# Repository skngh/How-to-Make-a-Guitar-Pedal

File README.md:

# How to Make a Digital Guitar Pedal

_by Sam Knight_

Welcome! This repository contains documentation and supporting materials for my YouTube course on how to build a digital guitar pedal using the Daisy Seed.

The goal of this course is not to clone a specific pedal, but to teach the full workflow and decision-making process behind designing, programming, and assembling your own digital guitar pedals.

## Table of Contents

- [Course Overview](#course-overview)
- [Prerequisites](#prerequisites)
- [Documentation & Resources](#documentation--resources)
  - [Bill of Materials](docs/bom.md)
  - [Resources & Links](docs/resources.md)
  - [Recommended Learning](docs/recommended-learning.md)
  - [Code](code/)
  - [Hardware](hardware/)
- [Episode Breakdown](#episode-breakdown)

## Course Overview

This course covers many topics, including:

- Setting up the **Daisy Seed** with a breadboard
- Programming a simple **hard clipping and soft clipping distortion**
- Using the **DaisySP library** to program the Daisy
- Making a **drill schematic on Tayda Electronics** for our enclosure
- Making a **full custom PCB in KiCad** with accurate part placements
- Designing a **graphic in Adobe Illustrator** to get **UV printed** onto our enclosure
- Ordering everything and **soldering** it all together

### Final Result

This does not mean it is the exact pedal you will end up with. The purpose of the course is to teach the fundamentals and workflow of digital pedal design, not to produce an identical clone. You are encouraged to experiment, modify, and build something that reflects your own ideas.

## Prerequisites!

This course is intended for beginners, but not all beginners start in the same place. While the course is designed to be approachable, there are areas where having absolutely no prior experience may create friction.

That said, even if you are completely new to this space, the course can still serve as a strong foundation. If your long-term goal is to design audio-related hardware or software, this course will help identify the gaps you may want to fill going forward.

You may find parts of the course challenging if you have no experience with the following:

1. **Basic programming.** I show you how to use the DaisySP library and teach very basic DSP, but if you haven't ever written a single line of code before, there will be confusing moments. I don't go over the very basics of programming in the course, but as long as you have a simple understanding of the building blocks of any programming language, then I think you'll be fine.
2. **Very basic understanding of electrical engineering.** Going forward, if something like a "resistor" means nothing to you, then you may hit a little bottleneck with designing pedals. Don't get me wrong, to design basic circuits like we do in this course, you don't have to design anything honestly, but if you want to keep improving that will be needed moving forward. And if you have zero understanding of wiring up components and things, then there may be moments of the course that get confusing.

## Episode Breakdown

### Episode 1 — Picking Parts

Setting up the Daisy Seed on a breadboard and selecting initial components so we can begin experimenting with knobs, switches, and basic interaction.

### Episode 2 — Basic DSP

An introduction to digital signal processing and the Daisy audio callback. We use these concepts to build simple hard-clipping and soft-clipping distortion effects.

### Episode 3 — DaisySP Library

A walkthrough of the DaisySP library and how to integrate its DSP modules into your projects. We implement a basic chorus effect as a practical example.

### Episode 4 — Enclosure Drill Schematic

Creating a drill schematic using Tayda Electronics so the enclosure arrives pre-drilled and ready for assembly.

### Episode 5 — Circuit Schematic

Designing a simple circuit schematic in KiCad to connect the Daisy Seed with external components.

### Episode 6 — Footprints

Learning how to find existing footprints and create custom footprints using component datasheets.

### Episode 7 — PCB Layout & Routing

Defining the PCB outline, placing components so the board fits correctly inside the enclosure and aligns with the drill schematic, and basic PCB routing and ground plane.

### Episode 8 — Design Review & Ordering

Verifying mechanical fit, checking for common errors, and ordering the PCB through PCBWay.

### Episode 9 — UV Printing & Final Parts Order

Designing enclosure artwork for UV printing and placing final parts orders.

### Episode 10 — Final Assembly

Soldering the pedal together, testing the hardware, and applying finishing touches to the firmware.

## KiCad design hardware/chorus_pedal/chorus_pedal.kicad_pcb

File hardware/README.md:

# Hardware

This folder contains all hardware-related files used throughout the course, including the PCB design, enclosure artwork, and drill schematic.

---

## PCB (KiCad)

The KiCad project files for the custom PCB designed during the course can be found in this folder.

- Open the KiCad project to view the schematic and PCB layout.
- These files correspond to [this code here.](../code/ChorusPedal/)

---

## Enclosure Graphic (Adobe Illustrator)

The enclosure artwork used for UV printing is provided as an Adobe Illustrator file.

- This file is used to generate the UV print design for Tayda.
- This is mostly for example and reference if you wanna checkout how I structured everything!

---

## Tayda Drill Schematic

Here is the Tayda drill schematic created during the course:

[Tayda Drill Schematic](https://drill.taydakits.com/box-designs/new?public_key=OXl2WFBpcTJRbzdteWcydDVlT2NJUT09Cg==)

This schematic ensures the enclosure arrives pre-drilled and aligned with the PCB layout.

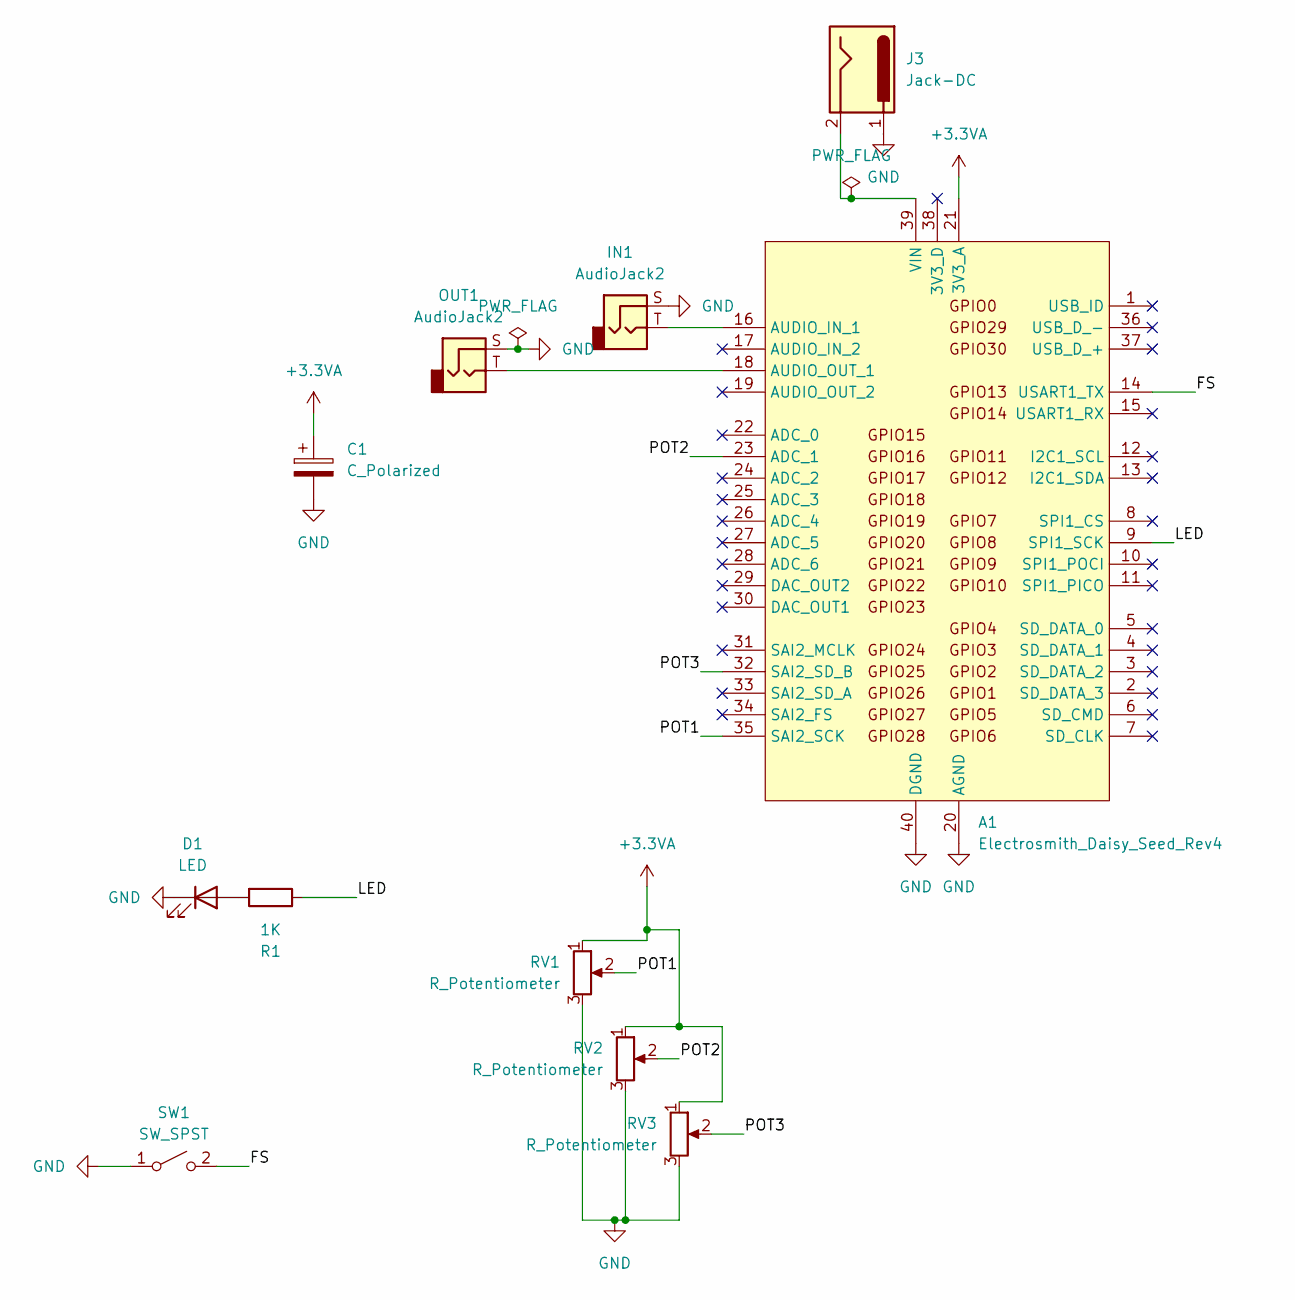
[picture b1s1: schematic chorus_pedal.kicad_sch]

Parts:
A1: Electrosmith_Daisy_Seed_Rev4; Electrosmith_Daisy_Seed
C1: C_Polarized; CP_Radial_D10.0mm_P2.50mm
D1: LED; LED_D5.0mm
IN1: AudioJack2; SolderWire-0.5sqmm_1x02_P4.6mm_D0.9mm_OD2.1mm
J3: Jack-DC; SolderWire-0.5sqmm_1x02_P4.6mm_D0.9mm_OD2.1mm
OUT1: AudioJack2; SolderWire-0.5sqmm_1x02_P4.6mm_D0.9mm_OD2.1mm
R1: 1K; R_Axial_DIN0207_L6.3mm_D2.5mm_P7.62mm_Horizontal
RV1, RV2, RV3: R_Potentiometer; RV16AF-41
SW1: SW_SPST; SolderWire-0.5sqmm_1x02_P4.6mm_D0.9mm_OD2.1mm

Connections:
+3.3VA: A1.21 (3V3_A), C1.1, RV1.1, RV2.1, RV3.1
/FS: A1.14 (USART1_TX), SW1.2 (B)
/LED: A1.9 (SPI1_SCK), R1.1
/POT1: A1.35 (SAI2_SCK), RV1.2
/POT2: A1.23 (ADC_1), RV2.2
/POT3: A1.32 (SAI2_SD_B), RV3.2
GND: A1.20 (AGND), A1.40 (DGND), C1.2, D1.1 (K), IN1.S, J3.1, OUT1.S, RV1.3, RV2.3, RV3.3, SW1.1 (A)
unnamed: A1.16 (AUDIO_IN_1), IN1.T
unnamed: A1.18 (AUDIO_OUT_1), OUT1.T
unnamed: A1.39 (VIN), J3.2
unnamed: D1.2 (A), R1.2

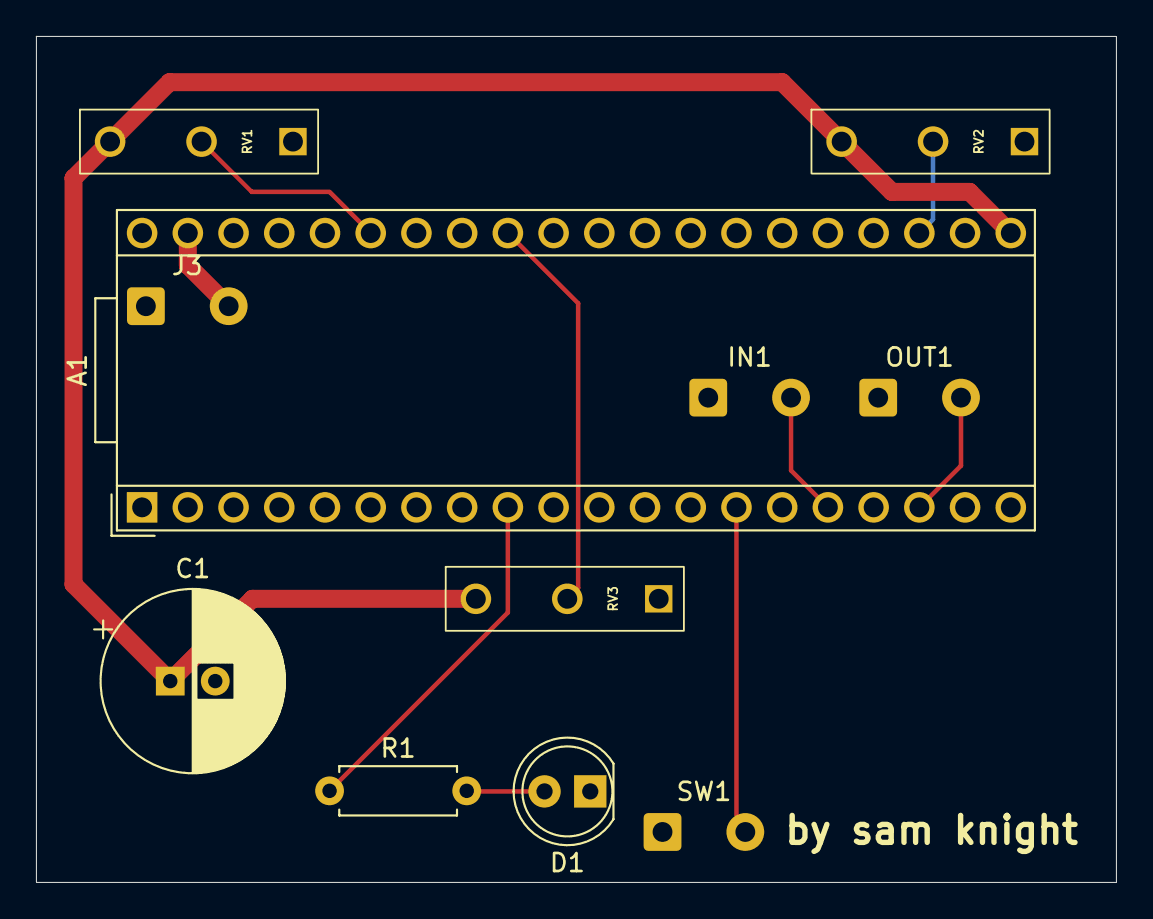
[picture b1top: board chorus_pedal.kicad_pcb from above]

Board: 2 copper layers, 60.0 x 47.0 mm, 11 parts (0 on the bottom side), 11 nets.

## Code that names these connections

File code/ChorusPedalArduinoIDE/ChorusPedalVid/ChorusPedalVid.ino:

#include "DaisyDuino.h"

DaisyHardware hw;

size_t num_channels;

#define LED D8
#define POT1 A1
#define POT2 A11
#define POT3 A10
#define FOOTSWITCH D13

bool bypass = true;

static MoogLadder lpf;
static Chorus chorus;
float feedback = 0.3;
float delayMs = 15;
float rate, depth, cutoff;

Switch footswitch;

void MyCallback(float **in, float **out, size_t size) {
  float wet;

  ProcessADC();

  for (size_t i = 0; i < size; i++) {
    wet = lpf.Process(chorus.Process(in[0][i]));


    out[0][i] = bypass ? in[0][i] : ((wet * 0.75) + (in[0][i] * 0.25));
  }
}

void setup() {
  float samplerate;
  // Initialize for Daisy pod at 48kHz
  hw = DAISY.init(DAISY_SEED, AUDIO_SR_48K);
  num_channels = hw.num_channels;
  samplerate = DAISY.get_samplerate();

  chorus.Init(samplerate);
  chorus.SetDelayMs(delayMs);
  chorus.SetFeedback(feedback);
  lpf.Init(samplerate);
  lpf.SetRes(0);


  pinMode(LED_BUILTIN, OUTPUT);
  pinMode(LED, OUTPUT);

  digitalWrite(LED_BUILTIN, HIGH);

  footswitch.Init(1000, true, FOOTSWITCH, INPUT_PULLUP);

  DAISY.begin(MyCallback);
}

void loop() {}
void ProcessADC()
{
  footswitch.Debounce();
  bypass ^= footswitch.RisingEdge();
  digitalWrite(LED, !bypass);

  rate = fmap(analogRead(POT1) / 1023.0, .1, 5, daisysp::Mapping::EXP);
  depth = fmap(analogRead(POT2) / 1023.0, 0, 1, daisysp::Mapping::EXP);
  cutoff = fmap(analogRead(POT3) / 1023.0, 500, 5000, daisysp::Mapping::LOG);

  chorus.SetLfoFreq(rate);
  chorus.SetLfoDepth(depth);
  lpf.SetFreq(cutoff);
}

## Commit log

2026-01-27 added everything
2026-01-30 added more sketches
2026-02-23 added defintions
2026-02-24 fixes
2026-03-11 added buffer/impedance resources
